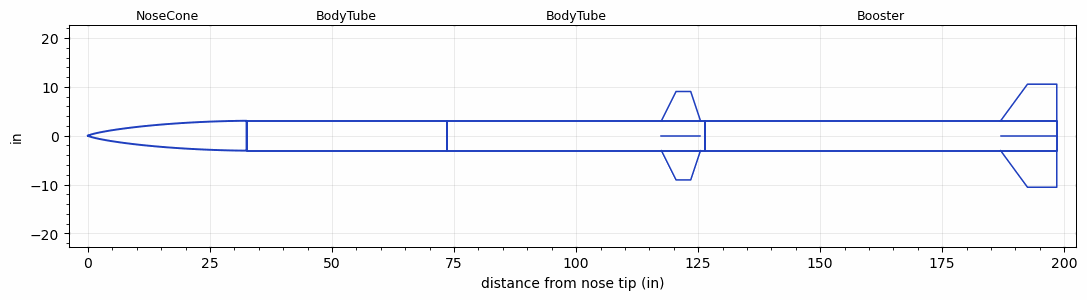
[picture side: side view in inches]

<RASAeroDocument>
 <FileVersion>2</FileVersion>
 <RocketDesign>
  <NoseCone>
   <Length>32.48</Length>
   <Diameter>6.12</Diameter>
   <Shape>LV-Haack</Shape>
   <Location>0</Location>
  </NoseCone>
  <BodyTube>
   <Length>41</Length>
   <Diameter>6.12</Diameter>
   <Location>32.48</Location>
  </BodyTube>
  <BodyTube>
   <Length>53</Length>
   <Diameter>6.12</Diameter>
   <Location>73.48</Location>
   <Fin>
    <Count>4</Count>
    <Chord>8</Chord>
    <Span>6</Span>
    <SweepDistance>3</SweepDistance>
    <TipChord>3</TipChord>
    <Thickness>0.188</Thickness>
    <Location>9</Location>
    <AirfoilSection>Rounded</AirfoilSection>
   </Fin>
  </BodyTube>
  <Booster>
   <Length>72</Length>
   <Diameter>6.12</Diameter>
   <InsideDiameter>6.12</InsideDiameter>
   <Location>126.48</Location>
   <ShoulderLength>0</ShoulderLength>
   <Fin>
    <Count>4</Count>
    <Chord>11.5</Chord>
    <Span>7.5</Span>
    <SweepDistance>5.5</SweepDistance>
    <TipChord>6</TipChord>
    <Thickness>0.188</Thickness>
    <Location>11.5</Location>
    <AirfoilSection>Rounded</AirfoilSection>
   </Fin>
  </Booster>
  <Surface>Rough Camouflage Paint</Surface>
  <ModifiedBarrowman>True</ModifiedBarrowman>
  <Turbulence>False</Turbulence>
  <UseBooster1>False</UseBooster1>
  <UseBooster2>False</UseBooster2>
 </RocketDesign>
 <LaunchSite>
  <Altitude>2782</Altitude>
  <Pressure>29.9</Pressure>
  <RodAngle>3</RodAngle>
  <RodLength>17</RodLength>
  <Temperature>95</Temperature>
  <WindSpeed>4.47</WindSpeed>
 </LaunchSite>
 <Recovery>
  <Altitude1>0</Altitude1>
  <Altitude2>0</Altitude2>
  <DeviceType1>None</DeviceType1>
  <DeviceType2>None</DeviceType2>
  <Event1>False</Event1>
  <Event2>False</Event2>
  <Size1>0</Size1>
  <Size2>0</Size2>
  <EventType1>None</EventType1>
  <EventType2>None</EventType2>
  <CD1>0</CD1>
  <CD2>0</CD2>
 </Recovery>
 <SimulationList>
  <Simulation>
   <SustainerEngine>O3621  (Coop)</SustainerEngine>
   <SustainerLaunchWt>114</SustainerLaunchWt>
   <SustainerNozzleDiameter>3</SustainerNozzleDiameter>
   <SustainerCG>86.3</SustainerCG>
   <SustainerIgnitionDelay>3</SustainerIgnitionDelay>
   <Booster1Engine>O5500X  (AT)</Booster1Engine>
   <Booster1LaunchWt>190</Booster1LaunchWt>
   <Booster1SeparationDelay>0.5</Booster1SeparationDelay>
   <Booster1IgnitionDelay>0</Booster1IgnitionDelay>
   <Booster1CG>118</Booster1CG>
   <Booster1NozzleDiameter>3</Booster1NozzleDiameter>
   <IncludeBooster1>True</IncludeBooster1>
   <Booster2Delay>0</Booster2Delay>
   <IncludeBooster2>False</IncludeBooster2>
   <TimetoApogee>57.09719</TimetoApogee>
   <MaxAltitude>47031.09</MaxAltitude>
   <MaxVelocity>2121.471</MaxVelocity>
  </Simulation>
  <Simulation>
   <SustainerEngine>N4000  (Aerotech)</SustainerEngine>
   <SustainerLaunchWt>71.6</SustainerLaunchWt>
   <SustainerNozzleDiameter>2.7</SustainerNozzleDiameter>
   <SustainerCG>80</SustainerCG>
   <SustainerIgnitionDelay>10</SustainerIgnitionDelay>
   <Booster1Engine>O5802  (Coop)</Booster1Engine>
   <Booster1LaunchWt>182</Booster1LaunchWt>
   <Booster1SeparationDelay>4</Booster1SeparationDelay>
   <Booster1IgnitionDelay>0</Booster1IgnitionDelay>
   <Booster1CG>132</Booster1CG>
   <Booster1NozzleDiameter>3.3</Booster1NozzleDiameter>
   <IncludeBooster1>True</IncludeBooster1>
   <Booster2Delay>0</Booster2Delay>
   <IncludeBooster2>False</IncludeBooster2>
   <TimetoApogee>61.0474</TimetoApogee>
   <MaxAltitude>46567.02</MaxAltitude>
   <MaxVelocity>2181.22</MaxVelocity>
  </Simulation>
  <Simulation>
   <SustainerEngine>O3688  (Coop)</SustainerEngine>
   <SustainerLaunchWt>113</SustainerLaunchWt>
   <SustainerNozzleDiameter>2.7</SustainerNozzleDiameter>
   <SustainerCG>86.22</SustainerCG>
   <SustainerIgnitionDelay>2</SustainerIgnitionDelay>
   <Booster1Engine>O5500X  (AT)</Booster1Engine>
   <Booster1LaunchWt>190</Booster1LaunchWt>
   <Booster1SeparationDelay>5</Booster1SeparationDelay>
   <Booster1IgnitionDelay>0</Booster1IgnitionDelay>
   <Booster1CG>118</Booster1CG>
   <Booster1NozzleDiameter>3.6</Booster1NozzleDiameter>
   <IncludeBooster1>True</IncludeBooster1>
   <Booster2Delay>0</Booster2Delay>
   <IncludeBooster2>False</IncludeBooster2>
   <TimetoApogee>58.91774</TimetoApogee>
   <MaxAltitude>45308.89</MaxAltitude>
   <MaxVelocity>2032.135</MaxVelocity>
  </Simulation>
 </SimulationList>
</RASAeroDocument>
